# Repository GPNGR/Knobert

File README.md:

# Knobert

Simple 4x3 macro pad with rotary encoder and OLED display

## Features

- EC-11 rotary encoder
- 0.91" 128x32 OLED
- cheap PCB (less than 100 mm x 100 mm)
- 3D printed enclosure
- per key led
- hot-swap
- QMK/Via/Vial compatible

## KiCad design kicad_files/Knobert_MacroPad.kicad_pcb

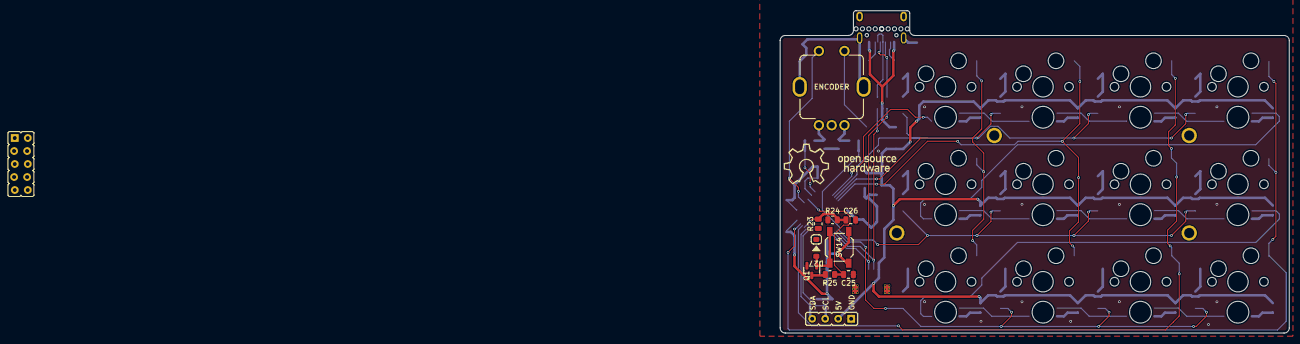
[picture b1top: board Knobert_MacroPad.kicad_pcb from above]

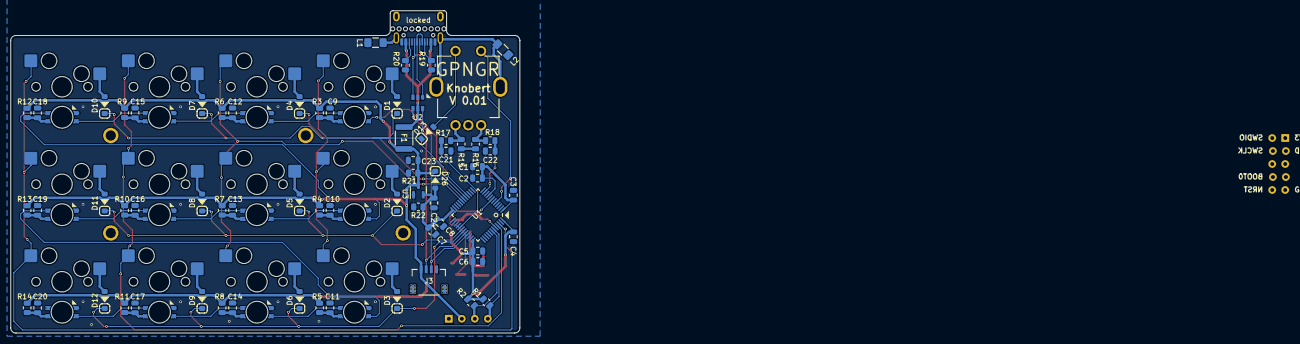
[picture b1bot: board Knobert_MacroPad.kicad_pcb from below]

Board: 2 copper layers, 99.5 x 63.0 mm, 110 parts (93 on the bottom side), 69 nets.

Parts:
C1: locked; C_0805_2012Metric
C2, C21, C22: 10n; C_0805_2012Metric
C3, C4, C5, C7, C9, C10, C11, C12, C13, C14, C15, C16, C17, C18, C19, C20, C25: 100n; C_0805_2012Metric
C6, C8: 4.7u; C_0805_2012Metric
C23, C24: 1u; C_0805_2012Metric
C26: 10u; C_0805_2012Metric
D1, D2, D3, D4, D5, D6, D7, D8, D9, D10, D11, D12, D13, D27: 1N4148W; D_SOD-123
D14, D15, D16, D17, D18, D19, D20, D21, D22, D23, D24, D25: SK6812MINI-E; SK6812MINI_3535_6028_3.2x2.8mm_Round
D26: RB060M-60TR; D_SOD-123
F1: mSMD110-16V; Fuse_1812_4532
H1, H2, H3, H4: MountingHole; MountingHole_2.5x4.0mm
H5, H6: MountingHole; MouseBite_IPC7351
H9: MountingHole; OSH_Logo_22.5x8.5mm
J1: ARM JTAG; PinHeader_2x5_P2.54mm_Vertical_Staggered
J3: Conn_01x04; SM04B-SRSS-TB(LF)(SN)_mounting-reliefs
J4: Oled; PinHeader_1x4_P2.54mm_Vertical
L1, L2: L_Ferrite; L_1206_3216Metric_Pad1.42x1.75mm_HandSolder
Q1: DTC123JKAT146; SOT-23
R1, R2: 4.7k; R_0805_2012Metric
R3, R4, R5, R6, R7, R8, R9, R10, R11, R12, R13, R14, R25: 100R; R_0805_2012Metric
R15, R16, R17, R18: 10k; R_0805_2012Metric
R19, R20: 5.1k; R_0805_2012Metric
R21, R22: 100k; R_0805_2012Metric
R23: 330k; R_0805_2012Metric
R24: 1M; R_0805_2012Metric
SW1, SW2, SW3, SW4, SW5, SW6, SW7, SW8, SW9, SW10, SW11, SW12: Mechanical_Switch; MX100H
SW13: EC11; ALPS_EC11E
SW14: SW_SPST; K2-1187SQ-A4SW-06
U1: STM32F072-LQFP48; LQFP-48_7x7mm_P0.5mm
U2: USBLC6-2SC6; SOT-23-6
U3: MCP1700-3302E; SOT-23
locked: locked; USB_C_Receptacle_Hroparts_TYPE-C-31-M-12

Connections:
3V3: C1.2, C2.2, C3.2, C4.1, C5.2, C6.2, C7.2, C8.2, C24.1, D26.2 (A), J1.1, R1.1, R2.1, R15.1, R16.1, R22.1, SW14.1 (A), U1.1 (VBAT), U1.9 (VDDA), U1.24 (VDD), U1.36 (VDDIO2), U1.48 (VDD), U3.2 (VO)
5V: C23.1, D26.1 (K), F1.2, J3.1, J4.2, R3.1, R4.1, R5.1, R6.1, R7.1, R8.1, R9.1, R10.1, R11.1, R12.1, R13.1, R14.1, R21.1, U3.3 (VI)
BOOT0: C26.2, J1.8, R23.1, R24.1, U1.44 (BOOT0)
C0: SW1.1, SW2.1, SW3.1, U1.18 (PB0/TIM3_CH3/ADC_IN8)
C1: SW4.1, SW5.1, SW6.1, U1.19 (PB1/TIM3_CH4/TIM14_CH1/ADC_IN9)
C2: SW7.1, SW8.1, SW9.1, U1.45 (I2C1_SCL/TIM16_CH1/PB8)
C3: SW10.1, SW11.1, SW12.1, U1.46 (SPI2_NSS/I2S2_WS/I2C1_SDA/TIM17_CH1/PB9)
C4: SW13.S2, U1.5 (PF0/OSC_IN)
CC1: R19.1, locked.A5 (CC1)
CC2: R20.1, locked.B5 (CC2)
D+: J3.3, U1.33 (USB_DP/PA12), U2.4 (I/O2)
D-: J3.2, U1.32 (USB_DM/TIM1_CH4/PA11), U2.6 (I/O1)
DBUS+: U2.3 (I/O2), locked.A6 (D+), locked.B6 (D+)
DBUS-: U2.1 (I/O1), locked.A7 (D-), locked.B7 (D-)
ENCODER_A: R15.2, R17.1, SW13.A
ENCODER_B: R16.2, R18.1, SW13.B
ENCODER_OUT_A: C21.2, R17.2, U1.29 (TIM1_CH1/PA8)
ENCODER_OUT_B: C22.2, R18.2, U1.11 (PA1/ADC_IN1)
ENCODER_SW1: D13.2 (A), SW13.S1
GND: C1.1, C2.1, C3.1, C4.2, C5.1, C6.1, C7.1, C8.1, C9.1, C10.1, C11.1, C12.1, C13.1, C14.1, C15.1, C16.1, C17.1, C18.1, C19.1, C20.1, C21.1, C22.1, C23.2, C24.2, C25.1, C26.1, D14.3 (VSS), D15.3 (VSS), D16.3 (VSS), D17.3 (VSS), D18.3 (VSS), D19.3 (VSS), D20.3 (VSS), D21.3 (VSS), D22.3 (VSS), D23.3 (VSS), D24.3 (VSS), D25.3 (VSS), J1.3, J1.9, J3.4, J4.1, L1.2, L2.2, Q1.2 (E), R19.2, R20.2, R21.2, R22.2, R24.2, SW13.C, U1.8 (VSSA), U1.23 (VSS), U1.35 (VSS), U1.47 (VSS), U2.2 (GND), U3.1 (GND), locked.A1 (GND), locked.B1 (GND)
GNDPWR: L1.1, L2.1, SW13.S (Shield)
LEDPWM: D14.4 (DIN), U1.16 (PA6/ADC_IN6/TIM3_CH1/TIM16_CH1)
NRST: C25.2, J1.10, R25.1, U1.7 (NRST)
unnamed: D1.2 (A), SW1.2
unnamed: D2.2 (A), SW2.2
unnamed: D3.2 (A), SW3.2
unnamed: D4.2 (A), SW4.2
unnamed: D5.2 (A), SW5.2
unnamed: D6.2 (A), SW6.2
unnamed: D7.2 (A), SW7.2
unnamed: D8.2 (A), SW8.2
unnamed: D9.2 (A), SW9.2
unnamed: D10.2 (A), SW10.2
unnamed: D11.2 (A), SW11.2
unnamed: D12.2 (A), SW12.2
unnamed: D14.2 (DOUT), D17.4 (DIN)
unnamed: C9.2, D14.1 (VDD), R3.2
unnamed: D15.4 (DIN), D23.2 (DOUT)
unnamed: D15.2 (DOUT), D18.4 (DIN)
unnamed: C10.2, D15.1 (VDD), R4.2
unnamed: D16.4 (DIN), D24.2 (DOUT)
unnamed: D16.2 (DOUT), D19.4 (DIN)
unnamed: C11.2, D16.1 (VDD), R5.2
unnamed: D17.2 (DOUT), D20.4 (DIN)
unnamed: C12.2, D17.1 (VDD), R6.2
unnamed: D18.2 (DOUT), D21.4 (DIN)
unnamed: C13.2, D18.1 (VDD), R7.2
unnamed: D19.2 (DOUT), D22.4 (DIN)
unnamed: C14.2, D19.1 (VDD), R8.2
unnamed: D20.2 (DOUT), D23.4 (DIN)
unnamed: C15.2, D20.1 (VDD), R9.2
unnamed: D21.2 (DOUT), D24.4 (DIN)
unnamed: C16.2, D21.1 (VDD), R10.2
unnamed: D22.2 (DOUT), D25.4 (DIN)
unnamed: C17.2, D22.1 (VDD), R11.2
unnamed: C18.2, D23.1 (VDD), R12.2
unnamed: C19.2, D24.1 (VDD), R13.2
unnamed: C20.2, D25.1 (VDD), R14.2
unnamed: D27.2 (A), Q1.1 (B), SW14.2 (B)
unnamed: D27.1 (K), R23.2
unnamed: Q1.3 (C), R25.2
R0: D1.1 (K), D4.1 (K), D7.1 (K), D10.1 (K), D13.1 (K), U1.17 (PA7/TIM3_CH2/TIM14_CH1/ADC_IN7)
R1: D2.1 (K), D5.1 (K), D8.1 (K), D11.1 (K), U1.30 (TIM1_CH2/PA9)
R2: D3.1 (K), D6.1 (K), D9.1 (K), D12.1 (K), U1.31 (TIM1_CH3/PA10)
SCL: J4.3, R2.2, U1.42 (I2C1_SCL/PB6)
SDA: J4.4, R1.2, U1.43 (2C1_SDA/PB7)
SWCLK: J1.4, U1.37 (SWCLK/PA14)
SWDIO: J1.2, U1.34 (SWDIO/PA13)
VBUS: F1.1, U2.5 (VBUS), locked.A4 (VBUS), locked.B4 (VBUS)

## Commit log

2023-01-21 Init kicad project with acheron libraries
2023-01-22 Added schematic
2023-01-22 Added mounting holes and jst connector
2023-01-22 Added oled
2023-01-29 beta pcb layout
